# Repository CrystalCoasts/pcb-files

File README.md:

# Smart Sea Wall PCB Files
Repo for ESP32 Smart Sea Wall PCB and Hardware.  
***

## Table of Contents
- [Introduction](#introduction)
- [Getting Started](#getting-started)
- [Layout](#contains)
- [Bill of Materials](#bill-of-materials)
- [Installation](#installation)

***

## Introduction

We designed and created a PCB for easy recreation of the device. The sensors are plug and play, allowing the user to easily service the device. The file was desgined in KiCAD and printed using JLC PCB.

***

## Getting Started

 1. Gather all components stated in the [BOM](#bill-of-materials).
 2. Order the PCB through JLCPCB using the already created gerber zip file.
 3. Follow the soldering and installation instructions in the [Instalation](#installation) section.
 4. Test device with the embedded-code repository.

## Bill of Materials

As far as materials go, many you may not be able to find headers the exact size for what you need. In that case, just find the closest one to it and cut it down to size (e.g. cut a 6 pin header to 5 pins), or use multiple to make up the size you need.

 - (8) 3-pin header
 - (4) SMA male connector
 - (2) 16-pin header
 - (2) 8-pin header
 - (1) 5-pin header
 - (2) 8-pin terminals (2.54 pitch)
 - (2) 3-pin terminals (2.54 pitch)
 - (3) 4.7k resistors (7.62 horizontal length)
 - (2) 1k resistors (7.62 horizontal length)
 - (2) bjt transistors (2n2222 or similar)
 - (1) mcp23017 I2C IO extender - [link](https://www.digikey.com/en/products/detail/microchip-technology/MCP23017-E-SP/894272)
 - (1) Boost converter - [link](https://a.co/d/0dH0B8B)
 - (1) I2C ADC - [link](https://www.adafruit.com/product/1083)
 - (1) Lilygo ESP32 T-7000G - [link](https://lilygo.cc/products/t-sim7000g?srsltid=AfmBOoofkf4orIAGPrCQvzU6p47uRy_uEcURHfCpysc8IG0x-OTQUHQe)

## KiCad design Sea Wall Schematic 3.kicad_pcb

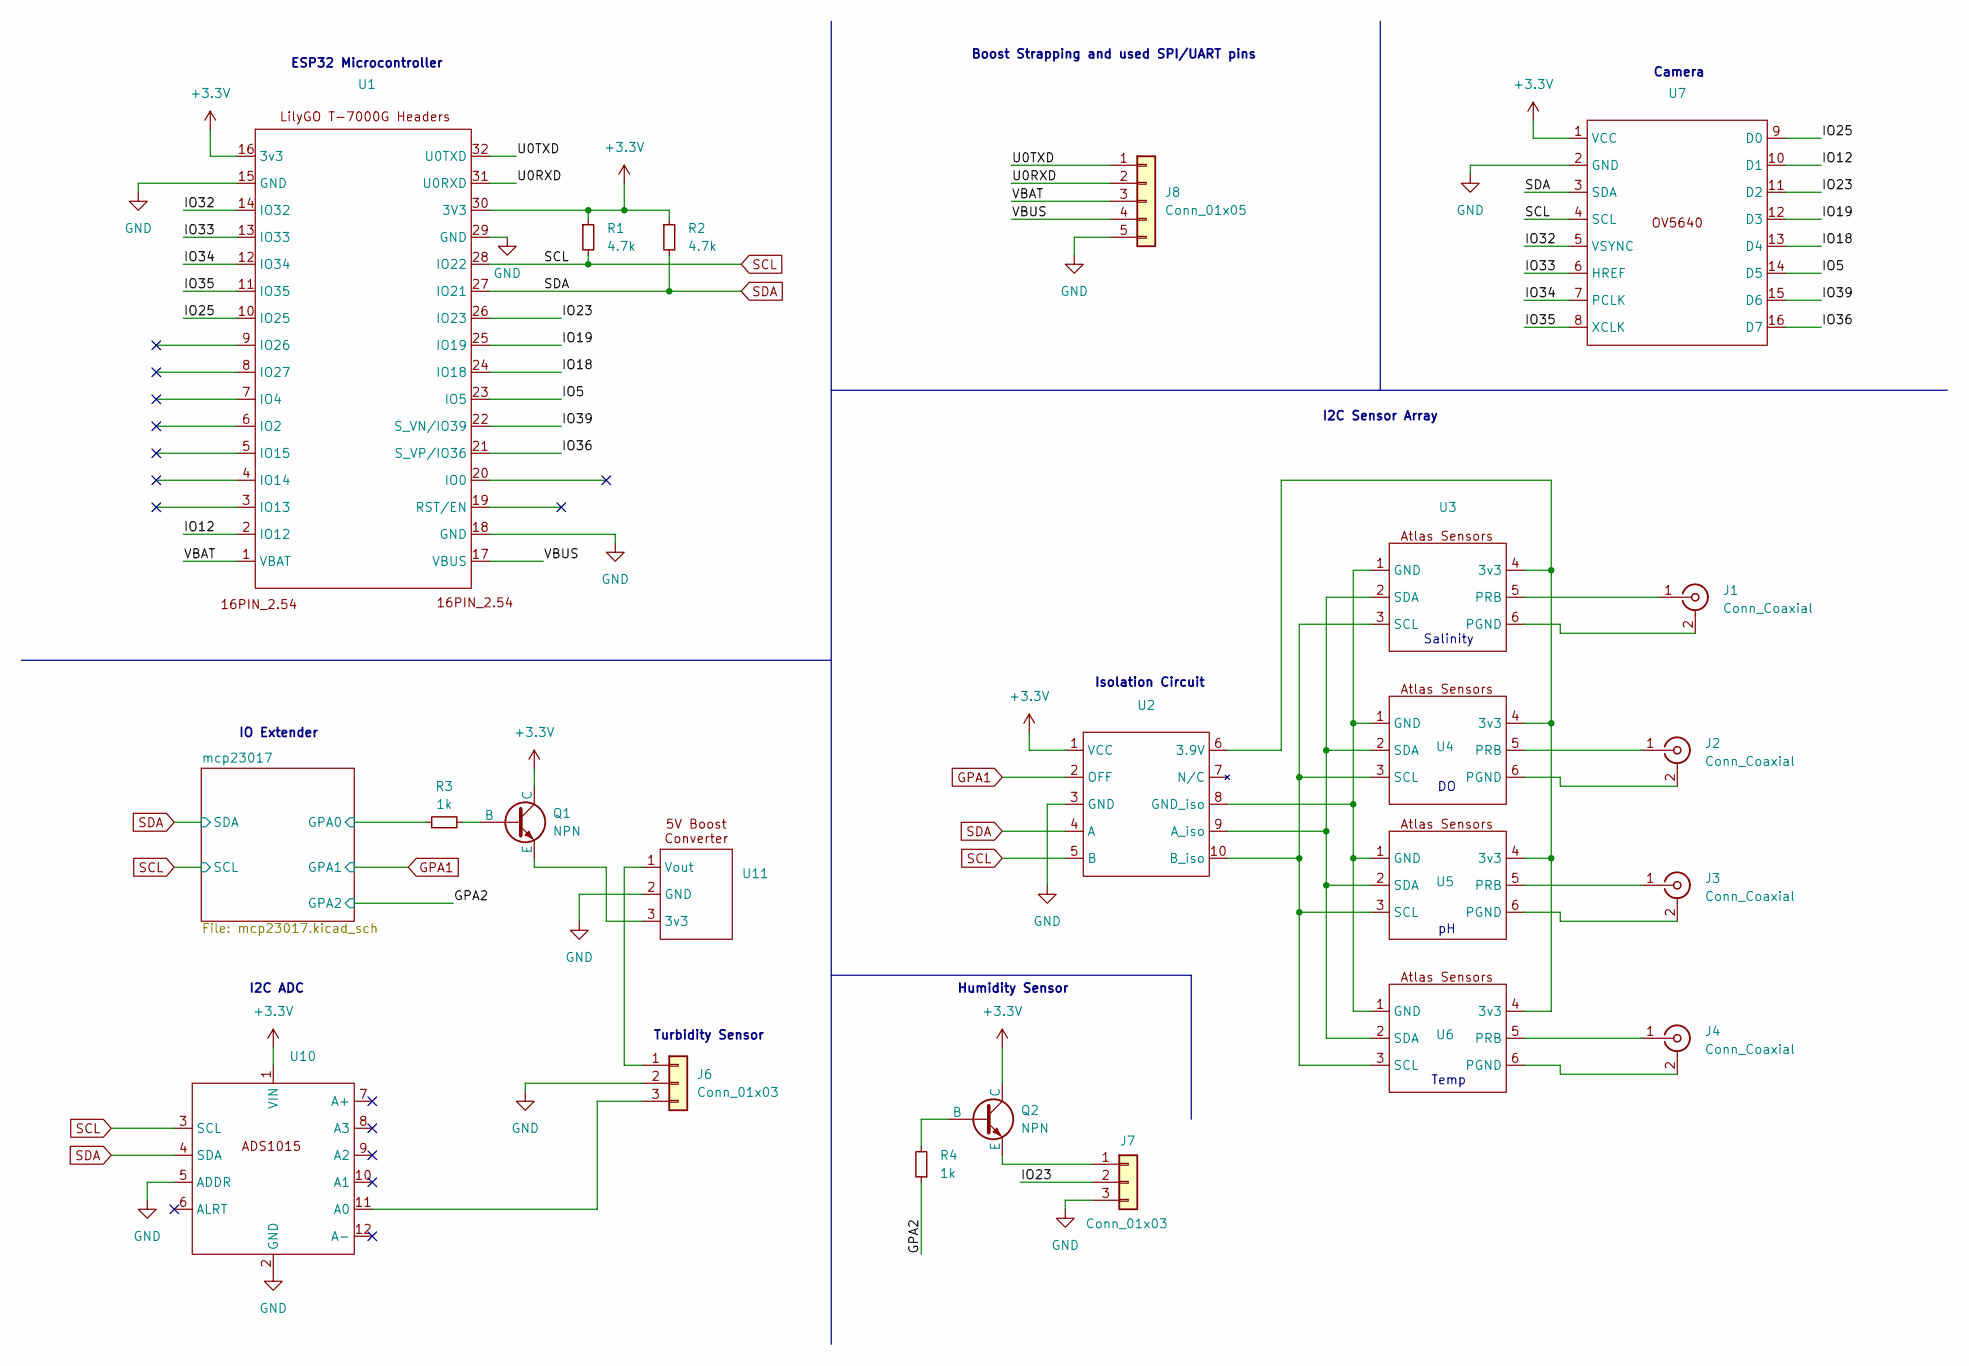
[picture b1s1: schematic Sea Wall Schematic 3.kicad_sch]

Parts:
J1, J2, J3, J4: Conn_Coaxial; SMA_Amphenol_901-144_Vertical
J6, J7: Conn_01x03; PinSocket_1x03_P2.54mm_Vertical
J8: Conn_01x05; PinHeader_1x05_P2.54mm_Vertical
Q1, Q2: NPN; TO-92
R1, R2: 4.7k; R_Axial_DIN0207_L6.3mm_D2.5mm_P7.62mm_Horizontal
R3, R4: 1k; R_Axial_DIN0207_L6.3mm_D2.5mm_P7.62mm_Horizontal
U1: T7000G
U2: isolation circuit
U3, U4, U5, U6: atlas-sensors
U7: OV5640
U10: AD1015
U11: boostconverter

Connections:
+3.3V: Q1.1 (C), Q2.1 (C), R1.1, R2.1, U1.16 (3v3), U1.30 (3V3), U2.1 (VCC), U7.1 (VCC), U10.1 (VIN); also elsewhere on the board
/GPA2: R4.1; also elsewhere on the board
/IO5: U1.23 (IO5), U7.14 (D5)
/IO12: U1.2 (IO12), U7.10 (D1)
/IO18: U1.24 (IO18), U7.13 (D4)
/IO19: U1.25 (IO19), U7.12 (D3)
/IO23: J7.2, U1.26 (IO23), U7.11 (D2)
/IO25: U1.10 (IO25), U7.9 (D0)
/IO32: U1.14 (IO32), U7.5 (VSYNC)
/IO33: U1.13 (IO33), U7.6 (HREF)
/IO34: U1.12 (IO34), U7.7 (PCLK)
/IO35: U1.11 (IO35), U7.8 (XCLK)
/IO36: U1.21 (S_VP/IO36), U7.16 (D7)
/IO39: U1.22 (S_VN/IO39), U7.15 (D6)
/U0RXD: J8.2, U1.31 (U0RXD)
/U0TXD: J8.1, U1.32 (U0TXD)
/VBAT: J8.3, U1.1 (VBAT)
/VBUS: J8.4, U1.17 (VBUS)
/mcp23017/GPA0: R3.1; also elsewhere on the board
GND: J6.2, J7.3, J8.5, U1.15 (GND), U1.18 (GND), U1.29 (GND), U2.3 (GND), U7.2 (GND), U10.2 (GND), U10.5 (ADDR), U11.2 (GND); also elsewhere on the board
GPA1: U2.2 (OFF); also elsewhere on the board
unnamed: J1.2 (Ext), U3.6 (PGND)
unnamed: J1.1 (In), U3.5 (PRB)
unnamed: J2.2 (Ext), U4.6 (PGND)
unnamed: J2.1 (In), U4.5 (PRB)
unnamed: J3.2 (Ext), U5.6 (PGND)
unnamed: J3.1 (In), U5.5 (PRB)
unnamed: J4.2 (Ext), U6.6 (PGND)
unnamed: J4.1 (In), U6.5 (PRB)
unnamed: J6.1, U11.1 (Vout)
unnamed: J6.3, U10.11 (A0)
unnamed: J7.1, Q2.3 (E)
unnamed: Q1.2 (B), R3.2
unnamed: Q1.3 (E), U11.3 (3v3)
unnamed: Q2.2 (B), R4.2
unnamed: U2.6 (3.9V), U3.4 (3v3), U4.4 (3v3), U5.4 (3v3), U6.4 (3v3)
unnamed: U2.9 (A_iso), U3.2 (SDA), U4.2 (SDA), U5.2 (SDA), U6.2 (SDA)
unnamed: U2.10 (B_iso), U3.3 (SCL), U4.3 (SCL), U5.3 (SCL), U6.3 (SCL)
unnamed: U2.8 (GND_iso), U3.1 (GND), U4.1 (GND), U5.1 (GND), U6.1 (GND)
SCL: R1.2, U1.28 (IO22), U2.5 (B), U7.4 (SCL), U10.3 (SCL); also elsewhere on the board
SDA: R2.2, U1.27 (IO21), U2.4 (A), U7.3 (SDA), U10.4 (SDA); also elsewhere on the board

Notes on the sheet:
Camera
Humidity Sensor
ESP32 Microcontroller
Isolation Circuit
Temp
Boost Strapping and used SPI/UART pins
Turbidity Sensor
IO Extender
I2C Sensor Array
Salinity
I2C ADC

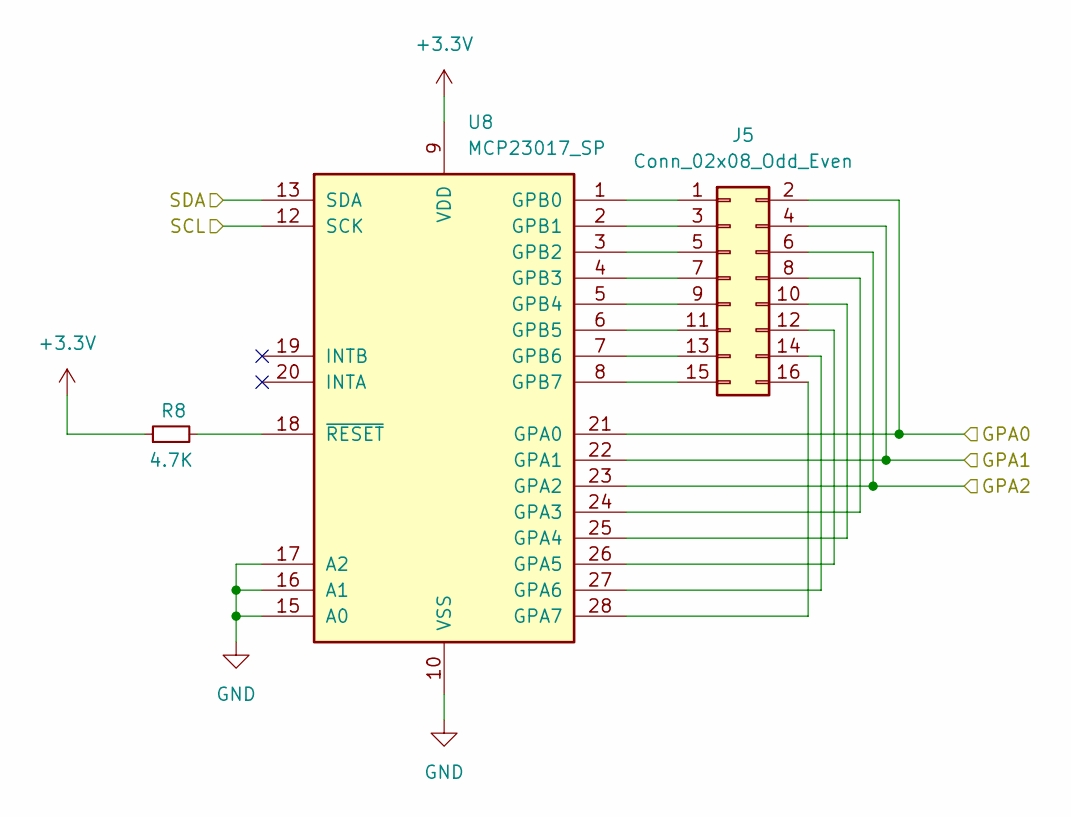
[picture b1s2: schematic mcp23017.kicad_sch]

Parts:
J5: Conn_02x08_Odd_Even; PinHeader_2x08_P2.54mm_Vertical
R8: 4.7K; R_Axial_DIN0207_L6.3mm_D2.5mm_P7.62mm_Horizontal
U8: MCP23017_SP; DIP-28_W7.62mm

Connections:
+3.3V: R8.1, U8.9 (VDD); also elsewhere on the board
/GPA2: J5.6, U8.23 (GPA2); also elsewhere on the board
/mcp23017/GPA0: J5.2, U8.21 (GPA0); also elsewhere on the board
GND: U8.10 (VSS), U8.15 (A0), U8.16 (A1), U8.17 (A2); also elsewhere on the board
GPA1: J5.4, U8.22 (GPA1); also elsewhere on the board
unnamed: J5.1, U8.1 (GPB0)
unnamed: J5.3, U8.2 (GPB1)
unnamed: J5.5, U8.3 (GPB2)
unnamed: J5.7, U8.4 (GPB3)
unnamed: J5.8, U8.24 (GPA3)
unnamed: J5.9, U8.5 (GPB4)
unnamed: J5.10, U8.25 (GPA4)
unnamed: J5.11, U8.6 (GPB5)
unnamed: J5.12, U8.26 (GPA5)
unnamed: J5.13, U8.7 (GPB6)
unnamed: J5.14, U8.27 (GPA6)
unnamed: J5.15, U8.8 (GPB7)
unnamed: J5.16, U8.28 (GPA7)
unnamed: R8.2, U8.18 (~RESET)
SCL: U8.12 (SCK); also elsewhere on the board
SDA: U8.13 (SDA); also elsewhere on the board

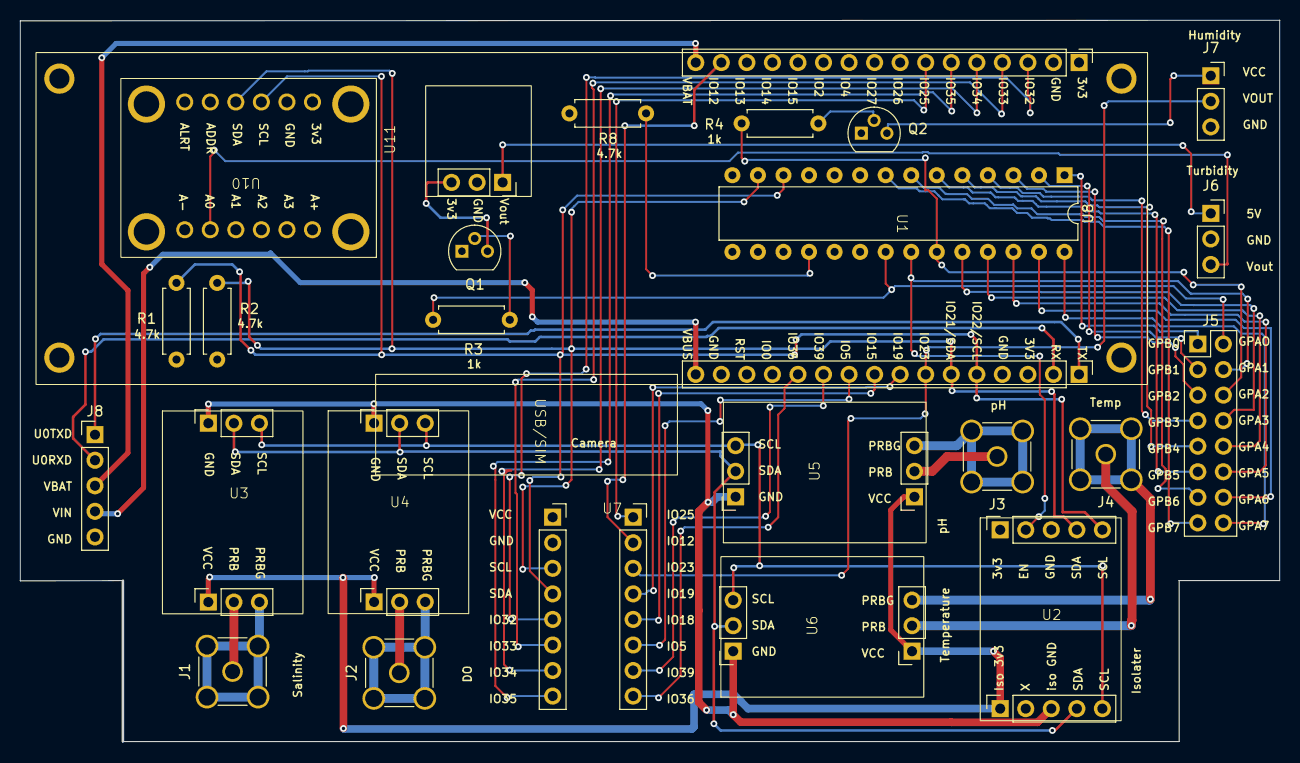
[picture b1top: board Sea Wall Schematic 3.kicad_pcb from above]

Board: 4 copper layers, 125.2 x 71.7 mm, 25 parts (0 on the bottom side), 55 nets.

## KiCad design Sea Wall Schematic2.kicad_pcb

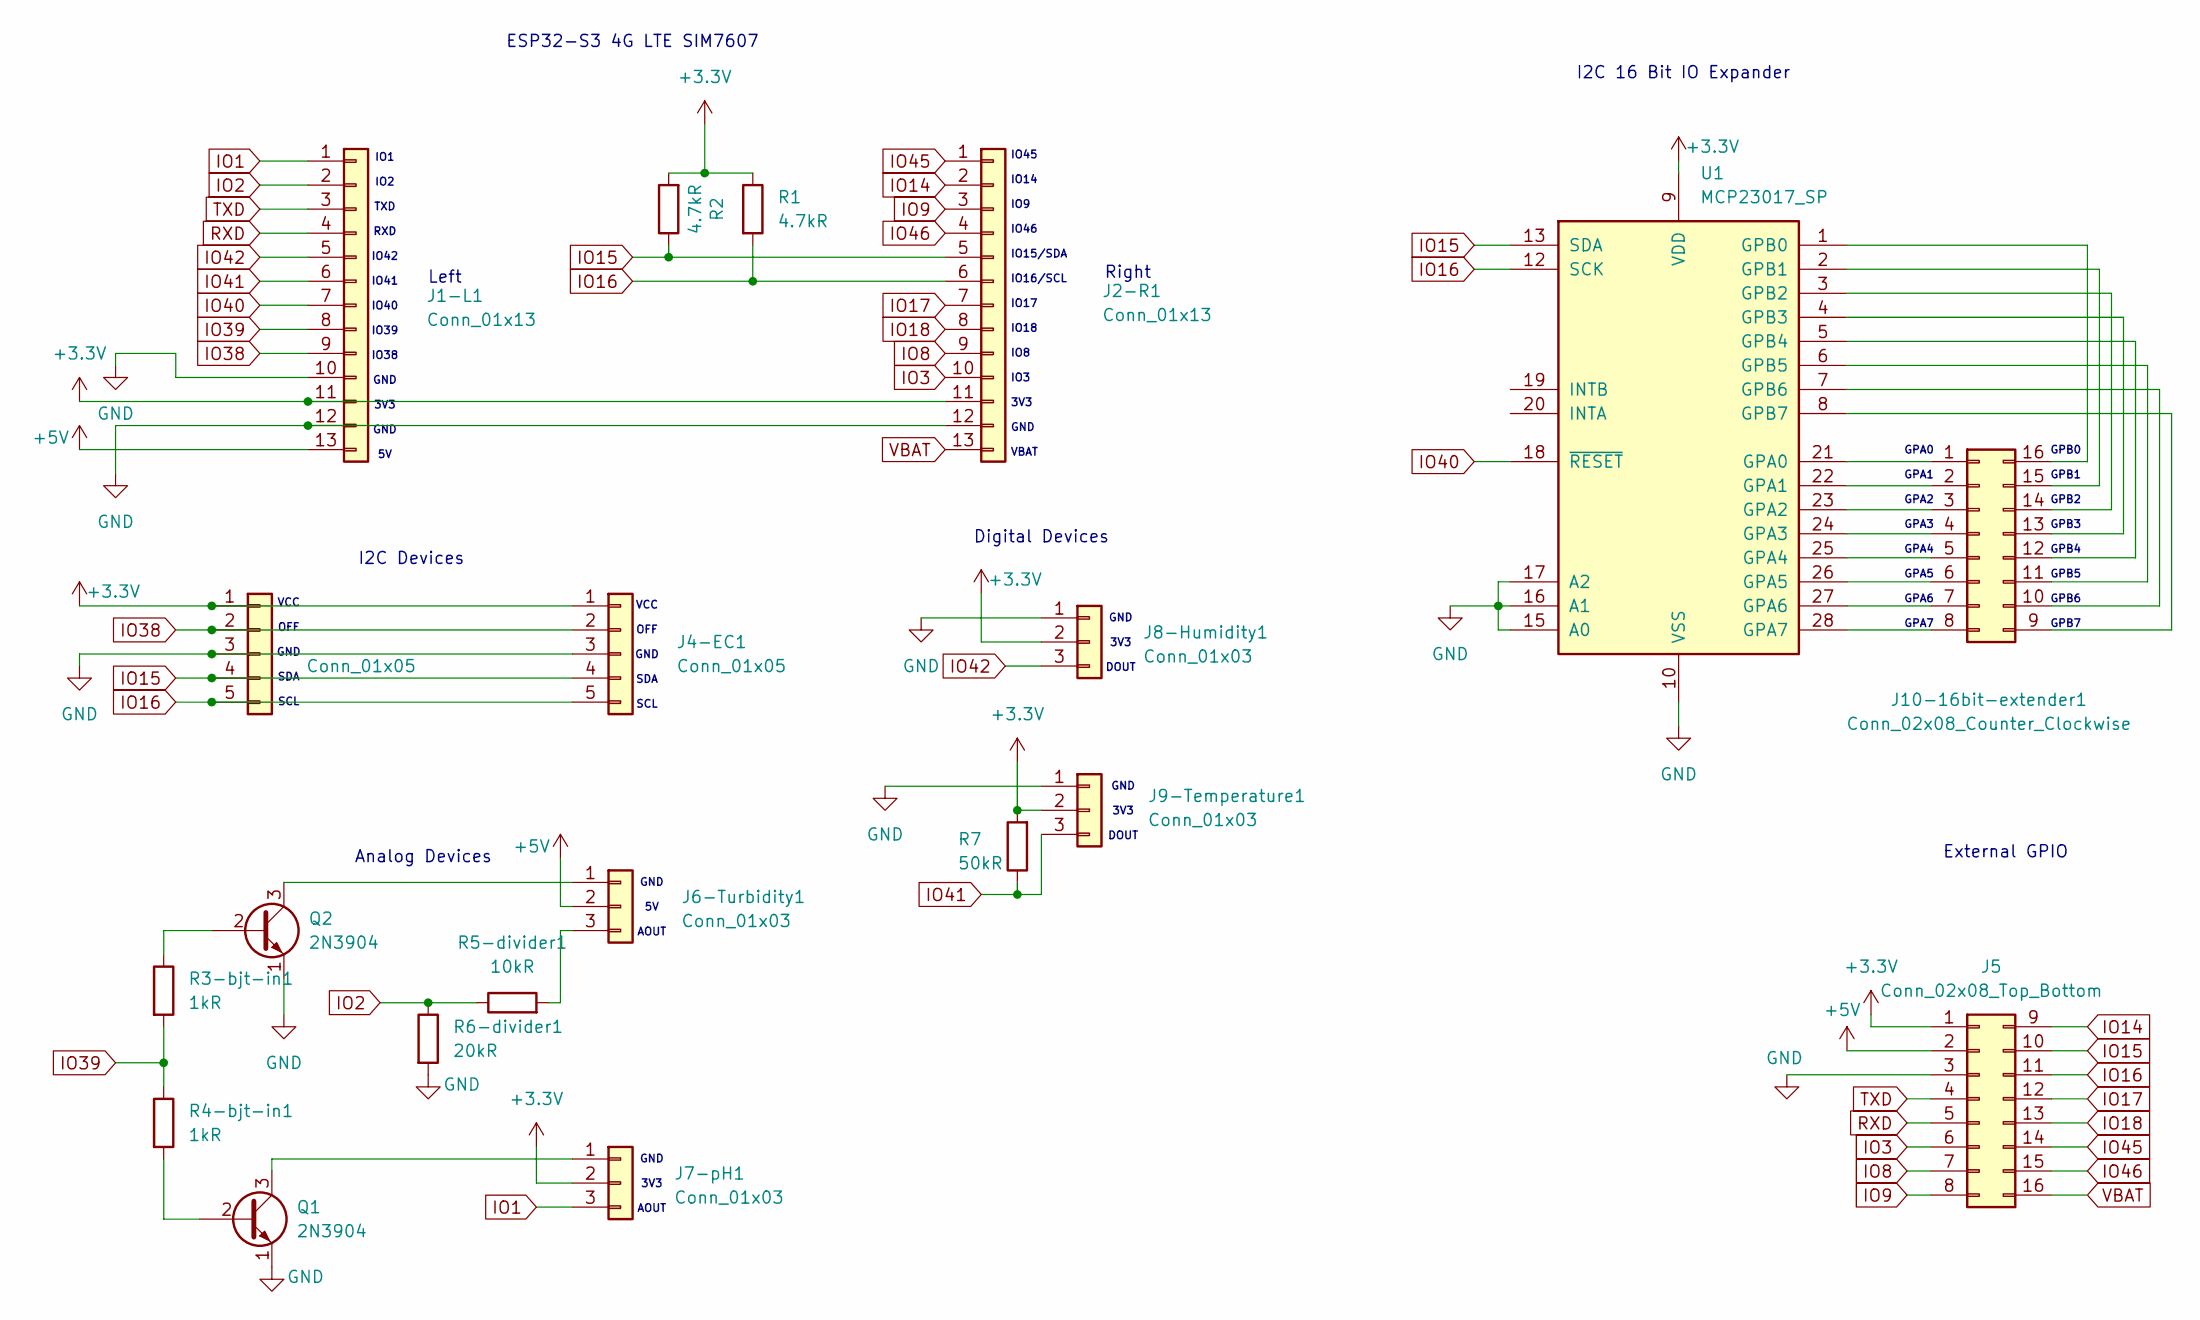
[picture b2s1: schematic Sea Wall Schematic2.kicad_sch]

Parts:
J1-L1, J2-R1: Conn_01x13; PinHeader_1x13_P2.54mm_Vertical
J3-DO1, J4-EC1: Conn_01x05; PinHeader_1x05_P2.54mm_Vertical
J5: Conn_02x08_Top_Bottom; PinHeader_2x08_P2.54mm_Vertical
J6-Turbidity1, J7-pH1, J8-Humidity1, J9-Temperature1: Conn_01x03; PinHeader_1x03_P2.54mm_Vertical
J10-16bit-extender1: Conn_02x08_Counter_Clockwise; PinHeader_2x08_P2.54mm_Vertical
Q1, Q2: 2N3904; TO-92_Inline
R1, R2: 4.7kR; R_Axial_DIN0204_L3.6mm_D1.6mm_P7.62mm_Horizontal
R3-bjt-in1, R4-bjt-in1: 1kR; R_Axial_DIN0204_L3.6mm_D1.6mm_P7.62mm_Horizontal
R5-divider1: 10kR; R_Axial_DIN0204_L3.6mm_D1.6mm_P7.62mm_Horizontal
R6-divider1: 20kR; R_Axial_DIN0204_L3.6mm_D1.6mm_P7.62mm_Horizontal
R7: 50kR; R_Axial_DIN0204_L3.6mm_D1.6mm_P7.62mm_Horizontal
U1: MCP23017_SP; DIP-28_W7.62mm

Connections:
+3.3V: J1-L1.11, J2-R1.11, J3-DO1.1, J4-EC1.1, J5.1, J7-pH1.2, J8-Humidity1.2, J9-Temperature1.2, R1.1, R2.2, R7.2, U1.9 (VDD)
+5V: J1-L1.13, J5.2, J6-Turbidity1.2
GND: J1-L1.10, J1-L1.12, J2-R1.12, J3-DO1.3, J4-EC1.3, J5.3, J8-Humidity1.1, J9-Temperature1.1, Q1.1 (E), Q2.1 (E), R6-divider1.2, U1.10 (VSS), U1.15 (A0), U1.16 (A1), U1.17 (A2)
IO1: J1-L1.1, J7-pH1.3
IO2: J1-L1.2, R5-divider1.1, R6-divider1.1
IO3: J2-R1.10, J5.6
IO8: J2-R1.9, J5.7
IO9: J2-R1.3, J5.8
IO14: J2-R1.2, J5.9
IO15: J2-R1.5, J3-DO1.4, J4-EC1.4, J5.10, R2.1, U1.13 (SDA)
IO16: J2-R1.6, J3-DO1.5, J4-EC1.5, J5.11, R1.2, U1.12 (SCK)
IO17: J2-R1.7, J5.12
IO18: J2-R1.8, J5.13
IO38: J1-L1.9, J3-DO1.2, J4-EC1.2
IO39: J1-L1.8, R3-bjt-in1.2, R4-bjt-in1.1
IO40: J1-L1.7, U1.18 (~RESET)
IO41: J1-L1.6, J9-Temperature1.3, R7.1
IO42: J1-L1.5, J8-Humidity1.3
IO45: J2-R1.1, J5.14
IO46: J2-R1.4, J5.15
unnamed: J6-Turbidity1.1, Q2.3 (C)
unnamed: J6-Turbidity1.3, R5-divider1.2
unnamed: J7-pH1.1, Q1.3 (C)
unnamed: J10-16bit-extender1.1, U1.21 (GPA0)
unnamed: J10-16bit-extender1.2, U1.22 (GPA1)
unnamed: J10-16bit-extender1.3, U1.23 (GPA2)
unnamed: J10-16bit-extender1.4, U1.24 (GPA3)
unnamed: J10-16bit-extender1.5, U1.25 (GPA4)
unnamed: J10-16bit-extender1.6, U1.26 (GPA5)
unnamed: J10-16bit-extender1.7, U1.27 (GPA6)
unnamed: J10-16bit-extender1.8, U1.28 (GPA7)
unnamed: J10-16bit-extender1.9, U1.8 (GPB7)
unnamed: J10-16bit-extender1.10, U1.7 (GPB6)
unnamed: J10-16bit-extender1.11, U1.6 (GPB5)
unnamed: J10-16bit-extender1.12, U1.5 (GPB4)
unnamed: J10-16bit-extender1.13, U1.4 (GPB3)
unnamed: J10-16bit-extender1.14, U1.3 (GPB2)
unnamed: J10-16bit-extender1.15, U1.2 (GPB1)
unnamed: J10-16bit-extender1.16, U1.1 (GPB0)
unnamed: Q1.2 (B), R4-bjt-in1.2
unnamed: Q2.2 (B), R3-bjt-in1.1
RXD: J1-L1.4, J5.5
TXD: J1-L1.3, J5.4
VBAT: J2-R1.13, J5.16

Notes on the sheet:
IO1 IO2 TXD RXD IO42 IO41 IO40 IO39 IO38 GND 3V3 GND 5V
ESP32-S3 4G LTE SIM7607
I2C Devices
Right
IO45 IO14 IO9 IO46 IO15/SDA IO16/SCL IO17 IO18 IO8 IO3 3V3 GND VBAT
External GPIO
GND 3V3 AOUT
Digital Devices
I2C 16 Bit IO Expander
GND 3V3 DOUT
GPB0 GPB1 GPB2 GPB3 GPB4 GPB5 GPB6 GPB7
VCC OFF GND SDA SCL
Left
Analog Devices
GND 5V AOUT
GPA0 GPA1 GPA2 GPA3 GPA4 GPA5 GPA6 GPA7

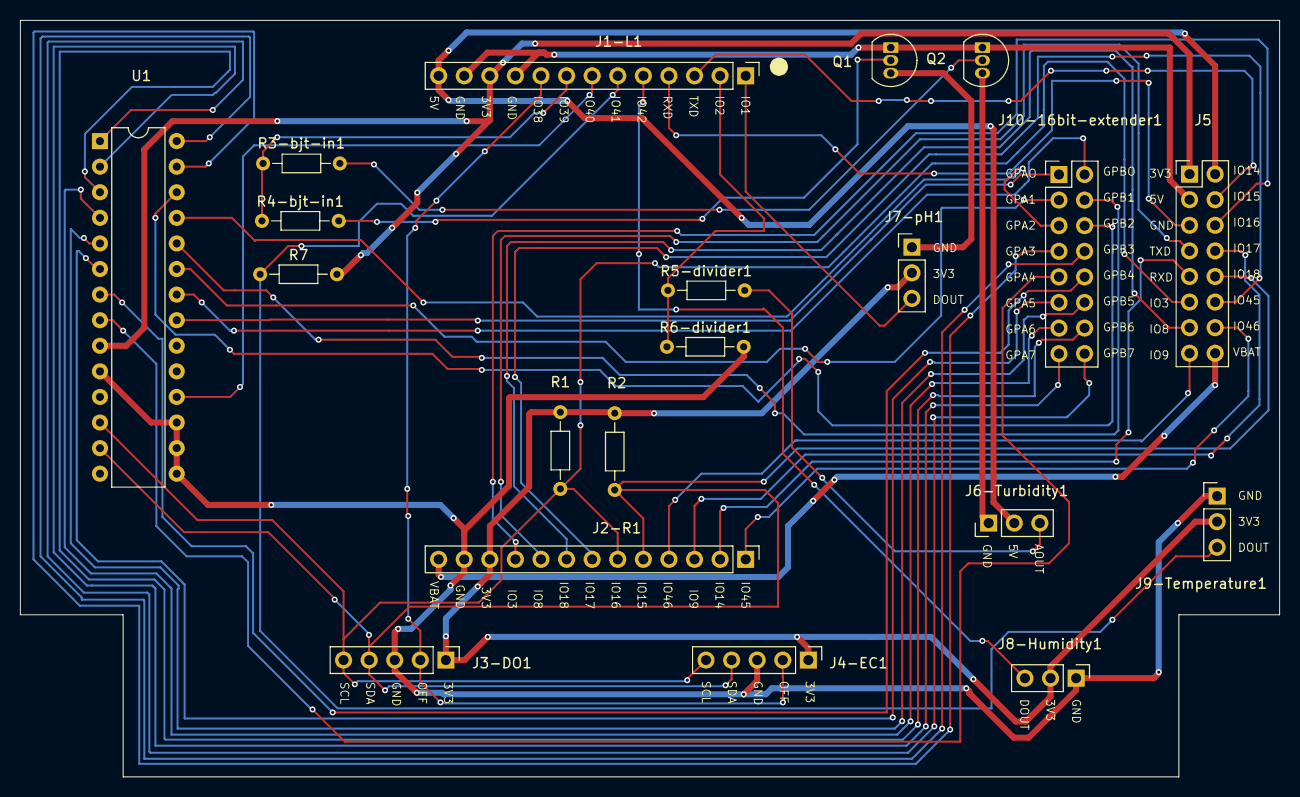
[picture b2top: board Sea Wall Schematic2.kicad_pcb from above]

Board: 2 copper layers, 125.0 x 75.1 mm, 20 parts (0 on the bottom side), 44 nets.

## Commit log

2024-12-04 PCB files for reproducing (Made in KiCad8)
2024-12-04 PCB Schematic PDF
2025-04-29 Updated PCB files from KiCAD
    updated gerbers and added zip files for the new schematic
